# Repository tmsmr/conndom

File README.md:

# conndom
*WiP*

### PCB

#### BOM

| Designator | Quantity | Designation | Mfr.     | Mfr. No.                | Comment |
|------------|----------|-------------|----------|-------------------------|---------|
| R1,R2      | 2        | 5.1 kohm    | -        | -                       | 0805    |
| J2         | 1        | USB A WIFI  | Same Sky | UJ2-AH-4-TH             |         |
| J1         | 1        | USB C PWR   | Same Sky | UJC-HP2-3-SMT-TR        |         |
| S1         | 1        | PWR BTN     | Same Sky | TS02-66-55-BK-260-LCR-D |         |
| R3         | 1        | 500 ohm     | -        | -                       | 0805    |
| D1         | 1        | SK6812      | Adafruit | 1655                    | 10 Pack |

### PCB Assembly

### PCB Assembly Bottom

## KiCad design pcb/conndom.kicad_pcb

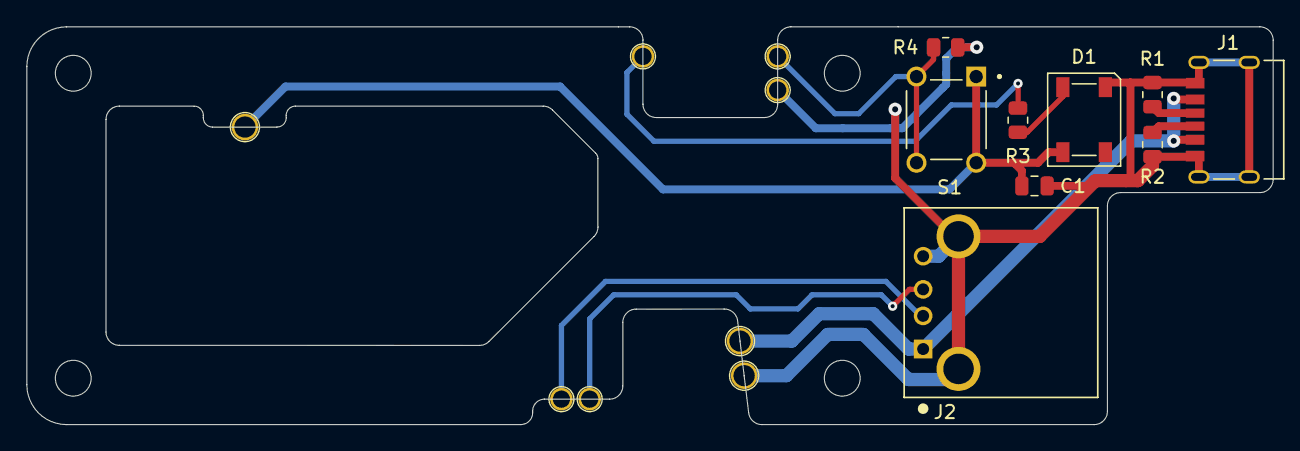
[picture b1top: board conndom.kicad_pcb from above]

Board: 2 copper layers, 94.0 x 30.0 mm, 17 parts (0 on the bottom side), 10 nets.

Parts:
C1: 104; C_0805_2012Metric
D1: SK6812; LED_SK6812_PLCC4_5.0x5.0mm_P3.2mm
J1: USB C PWR; CUI_UJC-HP2-3-SMT-TR
J2: USB A WIFI; CUI_UJ2-AH-4-TH
JG1: GND; 1.7mm-testpad-conn-plated
JG2: GPIO21; 1.7mm-testpad-conn-plated
JG3: GPIO12; 1.7mm-testpad-conn-plated
JT1: 5V; 2mm-testpad-conn-plated
JT2: GND; 2mm-testpad-conn-plated
JT3: USB_DP; 1.7mm-testpad-conn-plated
JT4: USB_DM; 1.7mm-testpad-conn-plated
JT5: 3V3; 2mm-testpad-conn-plated
R1, R2: 5K1; R_0805_2012Metric
R3: 500; R_0805_2012Metric
R4: 10k; R_0805_2012Metric
S1: PWR; SW_TS02-66-55-BK-260-LCR-D

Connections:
+5V: J1.A9 (VBUS), J1.B9 (VBUS__1), J2.1, JT1.1
GND: C1.1, D1.1 (VSS), J1.A12 (GND), J1.B12 (GND__1), J1.SH1 (SHIELD), J1.SH2 (SHIELD__1), J1.SH3 (SHIELD__2), J1.SH4 (SHIELD__3), J2.4, J2.SH1 (SHIELD), J2.SH2 (SHIELD__1), JG1.1, JT2.1, R1.2, R2.2, R4.1
unnamed: D1.2 (DIN), R3.2
unnamed: C1.2, D1.3 (VDD), JT5.1, S1.1, S1.2
unnamed: J1.A5 (CC1), R2.1
unnamed: J1.B5 (CC2), R1.1
unnamed: JG2.1, R4.2, S1.3, S1.4
unnamed: JG3.1, R3.1
unnamed: J2.3, JT3.1
unnamed: J2.2, JT4.1

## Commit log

2025-05-27 adds initial KiCad schematics
2025-05-27 adds rpi zero 2 w testpads submodule
2025-05-27 adds README and LICENSE
2025-06-02 first pcb design
2025-06-19 fix missplaced pads for usb dp, dm
2025-06-19 update step file
2025-06-19 update ref
2025-06-19 update footprints, renaming
2025-06-20 pcb rev 0.2
2025-06-20 valid drc exclusions
2025-06-21 only keep testpad connections locked
2025-06-21 update step export
2025-06-21 adds PCB screenshots
2025-06-21 DRC exclusions
2025-06-21 bom excludes
2025-06-21 adds BOM
2025-06-21 project files update
2025-06-21 adds gerbers
2025-06-23 bom for PCBWay WiP
2025-06-26 updates values in BOM
2025-07-03 new pcb layout with castellated holes
2025-07-20 docs for new pcb layout with castellated holes
2025-08-05 control software init
2025-10-26 🚀 adds devcontainer config
2025-10-31 ✨list wifi devices
2025-11-23 ✨ scan for wifi ap's
2025-11-23 ✨ merge ap's based on ssid, list stored connections
2025-11-23 ✨ add and delete networks
